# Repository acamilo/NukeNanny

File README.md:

# NukeNanny
Sensor Node for beehive data collection. 433mhz radio. temp/humidity/ optionally weight.

## Sensors
 * Humidity/Temp (HTU21D)
 * two optional load cells (HX711)

## Radio
 * 433mhz nrf9e5 8051 CPU + Radio
 * 10dBm Tx. 10mm helical antenna 2.5dBi
 
## Battery
 * CR2032 (225mAh)
 * [Rough power budget](https://docs.google.com/spreadsheets/d/1PkM406ndirrwiI1R5EvJM8zMfThP9lIQZCE76__e_ts/edit?usp=sharing) (avg draw 16uA)

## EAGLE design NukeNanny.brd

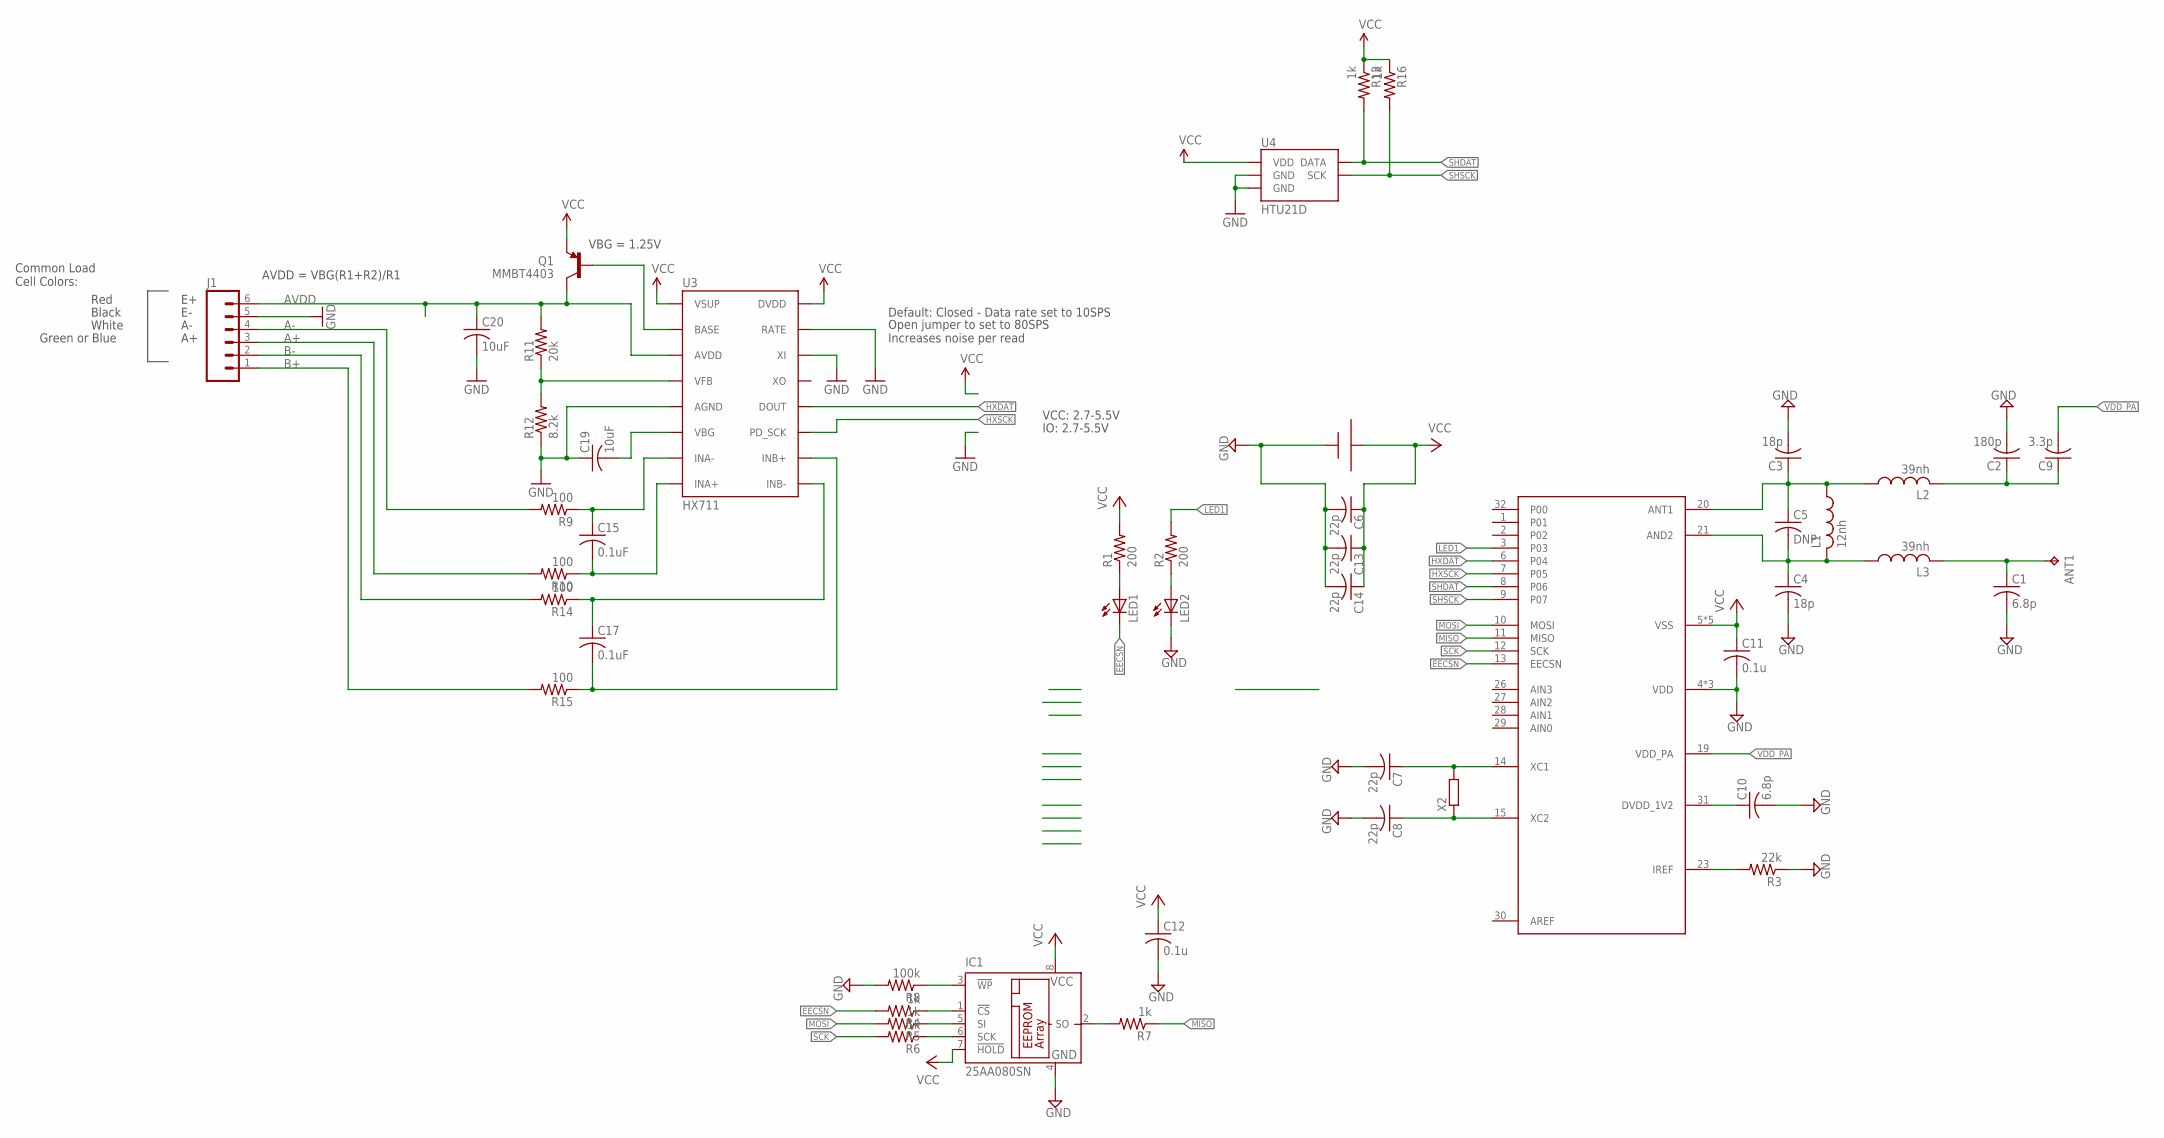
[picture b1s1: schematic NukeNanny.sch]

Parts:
ANT1: TPB2,54; B2,54
C1, C10: 6.8p; C0805
C2: 180p; C0805
C3, C4: 18p; C0805
C5: DNP; C0805
C6, C13, C14: 22p; C1206
C7, C8: 22p; C0805
C9: 3.3p; C0805
C11, C12: 0.1u; C0805
C15, C17: 0.1uF; C0805
C19, C20: 10uF; C0805
IC1: 25AA080SN; SO-08
J1: M06SMD-1MM; 1X06-1MM
L1: 12nh; L2012C
L2, L3: 39nh; L2012C
LED1, LED2: LEDCHIP-LED0805; CHIP-LED0805
Q1: MMBT4403; SOT23-3
R1, R2: 200; R0805
R3: 22k; R0805
R4, R5, R6, R7, R13, R16: 1k; R0805
R8: 100k; R0805
R9, R10, R14, R15: 100; R0805
R11: 20k; R0805
R12: 8.2k; R0805
U1: CR2032; SMT_CR2032_HOLDER
U3: HX711; SO16
U4: HTU21D
U$1: NRF9E5; 32QFN-THIN
X2: R-EU_R3225; R3225

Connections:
A+: J1.3, R10.2
A-: J1.4, R9.2
AVDD: C20.1, J1.6, Q1.3 (C), R11.2, U3.3 (AVDD)
B+: J1.1, R15.2
B-: J1.2, R14.2
EECSN: LED1.C, R4.2, U$1.13 (EECSN)
GND: C1.2, C2.2, C3.2, C4.2, C6.2, C7.2, C8.2, C10.2, C11.2, C12.2, C13.2, C14.2, C19.1, C20.2, IC1.4 (GND), J1.5, LED2.C, R3.1, R8.2, R12.1, U1.-, U3.5 (AGND), U3.14 (XI), U3.15 (RATE), U4.7 (GND), U4.GND, U$1.4 (VDD), U$1.17 (VDD), U$1.25 (VDD)
HXDAT: U3.12 (DOUT), U$1.6 (P04)
HXSCK: U3.11 (PD_SCK), U$1.7 (P05)
LED1: R2.2, U$1.3
MISO: R7.1, U$1.11 (MISO)
MOSI: R5.2, U$1.10 (MOSI)
unnamed: C4.1, C5.2, L1.2, L3.1, U$1.21 (AND2)
unnamed: C3.1, C5.1, L1.1, L2.1, U$1.20 (ANT1)
unnamed: C10.1, U$1.31 (DVDD_1V2)
unnamed: C2.1, C9.1, L2.2
unnamed: LED1.A, R1.1
unnamed: LED2.A, R2.1
unnamed: ANT1.TP, C1.1, L3.2
unnamed: C8.1, U$1.15 (XC2), X2.1
unnamed: C7.1, U$1.14 (XC1), X2.2
unnamed: IC1.1 (!CS), R4.1
unnamed: IC1.5 (SI), R5.1
unnamed: IC1.6 (SCK), R6.1
unnamed: IC1.2 (SO), R7.2
unnamed: R3.2, U$1.23 (IREF)
unnamed: IC1.3 (!WP), R8.1
unnamed: Q1.1 (B), U3.2 (BASE)
unnamed: R11.1, R12.2, U3.4 (VFB)
unnamed: C19.2, U3.6 (VBG)
unnamed: C17.1, R14.1, U3.9 (INB-)
unnamed: C15.1, R9.1, U3.7 (INA-)
unnamed: C15.2, R10.1, U3.8 (INA+)
unnamed: C17.2, R15.1, U3.10 (INB+)
SCK: R6.2, U$1.12 (SCK)
SHDAT: R13.2, U4.DATA, U$1.8 (P06)
SHSCK: R16.2, U4.SCK, U$1.9 (P07)
VCC: C6.1, C11.1, C12.1, C13.1, C14.1, IC1.7 (!HOLD), IC1.8 (VCC), Q1.2 (E), R1.2, R13.1, R16.1, U1.+, U3.1 (VSUP), U3.16 (DVDD), U4.VDD, U$1.5 (VSS), U$1.16 (VSS), U$1.18 (VSS), U$1.22 (VSS), U$1.24 (VSS)
VDD_PA: C9.2, U$1.19 (VDD_PA)

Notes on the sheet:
VCC: 2.7-5.5V
VBG = 1.25V
AVDD = VBG(R1+R2)/R1
Default: Closed - Data rate set to 10SPS
Open jumper to set to 80SPS Increases noise per read
Red
Black
White
Green or Blue
Common Load Cell Colors:
IO: 2.7-5.5V

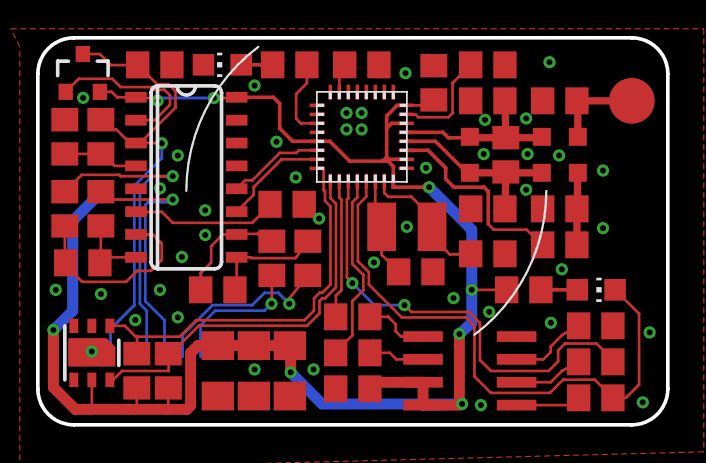
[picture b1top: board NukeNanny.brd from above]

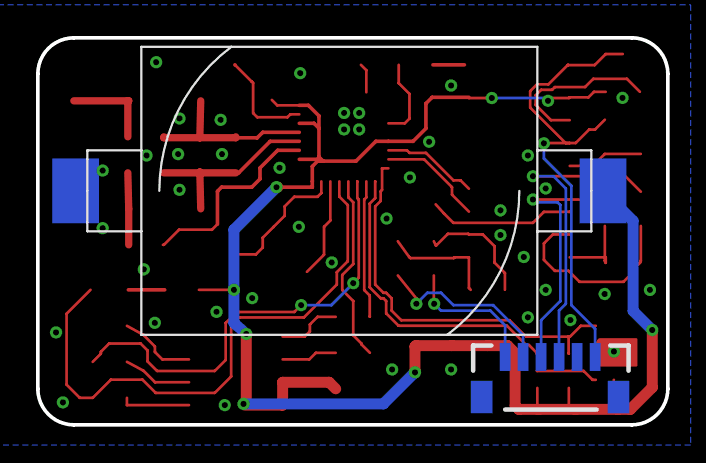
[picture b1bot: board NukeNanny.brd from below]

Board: 2 copper layers, 35.0 x 21.5 mm, 48 parts (2 on the bottom side), 39 nets.

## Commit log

2016-02-23 Layout done
2016-02-24 Changed sensor to HTU21D

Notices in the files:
parts and their libraries:
SparkFun-Sensors: Licensing: Creative Commons ShareAlike 4.0 International - https://creativecommons.org/licenses/by-sa/4.0
SparkFun-Connectors: Licensing: CC v3.0 Share-Alike You are welcome to use this library for commercial purposes.
